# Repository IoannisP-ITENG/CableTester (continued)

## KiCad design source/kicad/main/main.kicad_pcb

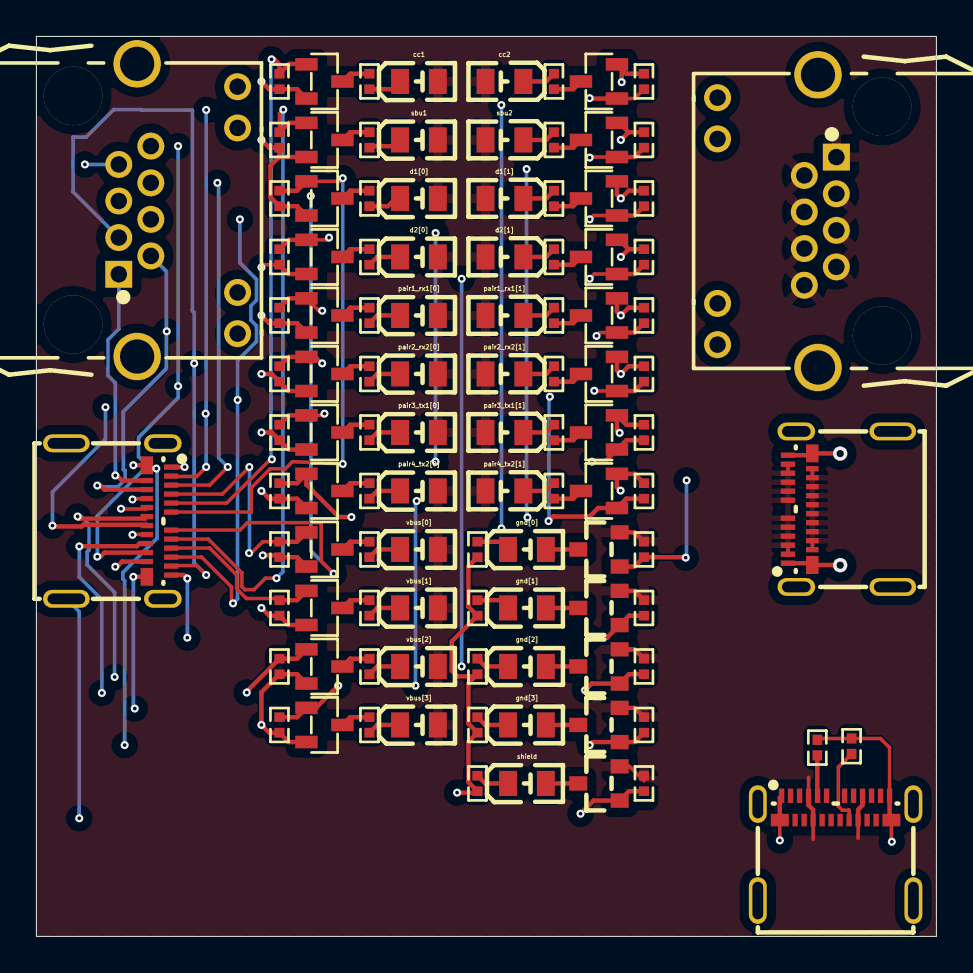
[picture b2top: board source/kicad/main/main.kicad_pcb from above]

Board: 4 copper layers, 50.0 x 50.0 mm, 107 parts (0 on the bottom side), 79 nets.

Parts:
psu.configuration_resistors[0][Resistor:5.0KΩ], psu.configuration_resistors[1][Resistor:5.0KΩ]: 5.0KΩ; R0402
psu.usb[USB_C_Receptacle:x]: x; USB-C-SMD_TYPE-C-USB-18
tester.cc1.indicator.led.current_limiting_resistor[Resistor:1KΩ], tester.cc2.indicator.led.current_limiting_resistor[Resistor:1KΩ], tester.d1[0].indicator.led.current_limiting_resistor[Resistor:1KΩ], tester.d1[1].indicator.led.current_limiting_resistor[Resistor:1KΩ], tester.d2[0].indicator.led.current_limiting_resistor[Resistor:1KΩ], tester.d2[1].indicator.led.current_limiting_resistor[Resistor:1KΩ], tester.gnd[0].indicator.led.current_limiting_resistor[Resistor:1KΩ], tester.gnd[1].indicator.led.current_limiting_resistor[Resistor:1KΩ], tester.gnd[2].indicator.led.current_limiting_resistor[Resistor:1KΩ], tester.gnd[3].indicator.led.current_limiting_resistor[Resistor:1KΩ], tester.pair1_rx1[0].indicator.led.current_limiting_resistor[Resistor:1KΩ], tester.pair1_rx1[1].indicator.led.current_limiting_resistor[Resistor:1KΩ], tester.pair2_rx2[0].indicator.led.current_limiting_resistor[Resistor:1KΩ], tester.pair2_rx2[1].indicator.led.current_limiting_resistor[Resistor:1KΩ], tester.pair3_tx1[0].indicator.led.current_limiting_resistor[Resistor:1KΩ], tester.pair3_tx1[1].indicator.led.current_limiting_resistor[Resistor:1KΩ], tester.pair4_tx2[0].indicator.led.current_limiting_resistor[Resistor:1KΩ], tester.pair4_tx2[1].indicator.led.current_limiting_resistor[Resistor:1KΩ], tester.sbu1.indicator.led.current_limiting_resistor[Resistor:1KΩ], tester.sbu2.indicator.led.current_limiting_resistor[Resistor:1KΩ], tester.shield.indicator.led.current_limiting_resistor[Resistor:1KΩ], tester.vbus[0].indicator.led.current_limiting_resistor[Resistor:1KΩ], tester.vbus[1].indicator.led.current_limiting_resistor[Resistor:1KΩ], tester.vbus[2].indicator.led.current_limiting_resistor[Resistor:1KΩ], tester.vbus[3].indicator.led.current_limiting_resistor[Resistor:1KΩ]: 1KΩ; R0402
tester.cc1.indicator.led.led[LED:D], tester.cc2.indicator.led.led[LED:D], tester.d1[0].indicator.led.led[LED:D], tester.d1[1].indicator.led.led[LED:D], tester.d2[0].indicator.led.led[LED:D], tester.d2[1].indicator.led.led[LED:D], tester.gnd[0].indicator.led.led[LED:D], tester.gnd[1].indicator.led.led[LED:D], tester.gnd[2].indicator.led.led[LED:D], tester.gnd[3].indicator.led.led[LED:D], tester.pair1_rx1[0].indicator.led.led[LED:D], tester.pair1_rx1[1].indicator.led.led[LED:D], tester.pair2_rx2[0].indicator.led.led[LED:D], tester.pair2_rx2[1].indicator.led.led[LED:D], tester.pair3_tx1[0].indicator.led.led[LED:D], tester.pair3_tx1[1].indicator.led.led[LED:D], tester.pair4_tx2[0].indicator.led.led[LED:D], tester.pair4_tx2[1].indicator.led.led[LED:D], tester.sbu1.indicator.led.led[LED:D], tester.sbu2.indicator.led.led[LED:D], tester.shield.indicator.led.led[LED:D], tester.vbus[0].indicator.led.led[LED:D], tester.vbus[1].indicator.led.led[LED:D], tester.vbus[2].indicator.led.led[LED:D], tester.vbus[3].indicator.led.led[LED:D]: D; LED0805-R-RD
tester.cc1.indicator.power_switch.mosfet[MOSFET:Q], tester.cc2.indicator.power_switch.mosfet[MOSFET:Q], tester.d1[0].indicator.power_switch.mosfet[MOSFET:Q], tester.d1[1].indicator.power_switch.mosfet[MOSFET:Q], tester.d2[0].indicator.power_switch.mosfet[MOSFET:Q], tester.d2[1].indicator.power_switch.mosfet[MOSFET:Q], tester.pair1_rx1[0].indicator.power_switch.mosfet[MOSFET:Q], tester.pair1_rx1[1].indicator.power_switch.mosfet[MOSFET:Q], tester.pair2_rx2[0].indicator.power_switch.mosfet[MOSFET:Q], tester.pair2_rx2[1].indicator.power_switch.mosfet[MOSFET:Q], tester.pair3_tx1[0].indicator.power_switch.mosfet[MOSFET:Q], tester.pair3_tx1[1].indicator.power_switch.mosfet[MOSFET:Q], tester.pair4_tx2[0].indicator.power_switch.mosfet[MOSFET:Q], tester.pair4_tx2[1].indicator.power_switch.mosfet[MOSFET:Q], tester.sbu1.indicator.power_switch.mosfet[MOSFET:Q], tester.sbu2.indicator.power_switch.mosfet[MOSFET:Q], tester.vbus[0].indicator.power_switch.mosfet[MOSFET:Q], tester.vbus[1].indicator.power_switch.mosfet[MOSFET:Q], tester.vbus[2].indicator.power_switch.mosfet[MOSFET:Q], tester.vbus[3].indicator.power_switch.mosfet[MOSFET:Q]: Q; SOT-23-3_L2.9-W1.3-P1.90-LS2.4-BR
tester.cc1.indicator.power_switch.pull_resistor[Resistor:100KΩ], tester.cc2.indicator.power_switch.pull_resistor[Resistor:100KΩ], tester.d1[0].indicator.power_switch.pull_resistor[Resistor:100KΩ], tester.d1[1].indicator.power_switch.pull_resistor[Resistor:100KΩ], tester.d2[0].indicator.power_switch.pull_resistor[Resistor:100KΩ], tester.d2[1].indicator.power_switch.pull_resistor[Resistor:100KΩ], tester.gnd[0].indicator.power_switch.pull_resistor[Resistor:100KΩ], tester.gnd[1].indicator.power_switch.pull_resistor[Resistor:100KΩ], tester.gnd[2].indicator.power_switch.pull_resistor[Resistor:100KΩ], tester.gnd[3].indicator.power_switch.pull_resistor[Resistor:100KΩ], tester.pair1_rx1[0].indicator.power_switch.pull_resistor[Resistor:100KΩ], tester.pair1_rx1[1].indicator.power_switch.pull_resistor[Resistor:100KΩ], tester.pair2_rx2[0].indicator.power_switch.pull_resistor[Resistor:100KΩ], tester.pair2_rx2[1].indicator.power_switch.pull_resistor[Resistor:100KΩ], tester.pair3_tx1[0].indicator.power_switch.pull_resistor[Resistor:100KΩ], tester.pair3_tx1[1].indicator.power_switch.pull_resistor[Resistor:100KΩ], tester.pair4_tx2[0].indicator.power_switch.pull_resistor[Resistor:100KΩ], tester.pair4_tx2[1].indicator.power_switch.pull_resistor[Resistor:100KΩ], tester.sbu1.indicator.power_switch.pull_resistor[Resistor:100KΩ], tester.sbu2.indicator.power_switch.pull_resistor[Resistor:100KΩ], tester.shield.indicator.power_switch.pull_resistor[Resistor:100KΩ], tester.vbus[0].indicator.power_switch.pull_resistor[Resistor:100KΩ], tester.vbus[1].indicator.power_switch.pull_resistor[Resistor:100KΩ], tester.vbus[2].indicator.power_switch.pull_resistor[Resistor:100KΩ], tester.vbus[3].indicator.power_switch.pull_resistor[Resistor:100KΩ]: 100KΩ; R0402
tester.gnd[0].indicator.power_switch.mosfet[MOSFET:Q], tester.gnd[1].indicator.power_switch.mosfet[MOSFET:Q], tester.gnd[2].indicator.power_switch.mosfet[MOSFET:Q], tester.gnd[3].indicator.power_switch.mosfet[MOSFET:Q], tester.shield.indicator.power_switch.mosfet[MOSFET:Q]: Q; SOT-23_L2.9-W1.3-P1.90-LS2.4-BR
tester.rj45[0][RJ45_Receptacle:x], tester.rj45[1][RJ45_Receptacle:x]: x; RJ45-TH_B-1-1
tester.usb_c[0][USB_C_Receptacle:x], tester.usb_c[1][USB_C_Receptacle:x]: x; USB-C-SMD_TYPE-C-USB-18

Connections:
psu.usb[USB_C_Receptacle:x]-psu.configuration_resistors[0][Resistor:5.0KΩ]: psu.configuration_resistors[0][Resistor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.1, psu.usb[USB_C_Receptacle:x].A5
psu.usb[USB_C_Receptacle:x]-psu.configuration_resistors[1][Resistor:5.0KΩ]: psu.configuration_resistors[1][Resistor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.1, psu.usb[USB_C_Receptacle:x].B5
tester.cc1.indicator.led.current_limiting_resistor[Resistor:1KΩ]-tester.cc1.ind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: tester.cc1.indicator.led.current_limiti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.2, tester.cc1.indicator.led.led[LED:D].2
tester.cc1.indicator.power_switch[PowerSwitch:virt]:5-tester.cc1.indicator.led[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: tester.cc1.indicator.led.current_limiti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.1, tester.cc1.indicator.power_switch.mosfe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.3
tester.cc1.indicator[LEDIndicator:virt]-tester.cc1.indicator.power_switch[Power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: tester.cc1.indicator.power_switch.mosfe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.1, tester.cc1.indicator.power_switch.pull_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.1, tester.usb_c[1][USB_C_Receptacle:x].A5
tester.cc2.indicator.led.led[LED:D]-tester.cc2.indicator.led.current_limiting_r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: tester.cc2.indicator.led.current_limiti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.2, tester.cc2.indicator.led.led[LED:D].2
tester.cc2.indicator.power_switch[PowerSwitch:virt]-tester.cc2.indicator[LEDInd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: tester.cc2.indicator.power_switch.mosfe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.1, tester.cc2.indicator.power_switch.pull_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.1, tester.usb_c[1][USB_C_Receptacle:x].B5
tester.cc2.indicator.power_switch[PowerSwitch:virt]:5-tester.cc2.indicator.led[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: tester.cc2.indicator.led.current_limiti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.1, tester.cc2.indicator.power_switch.mosfe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.3
tester.d1[0].indicator.led.current_limiting_resistor[Resistor:1KΩ]-tester.d1[0]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: tester.d1[0].indicator.led.current_limi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.2, tester.d1[0].indicator.led.led[LED:D].2
tester.d1[0].indicator.led[PoweredLED:virt]:2-tester.d1[0].indicator.power_swit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: tester.d1[0].indicator.led.current_limi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.1, tester.d1[0].indicator.power_switch.mos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.3
tester.d1[0].indicator[LEDIndicator:virt]-tester.d1[0].indicator.power_switch[P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: tester.d1[0].indicator.power_switch.mos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.1, tester.d1[0].indicator.power_switch.pul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.1, tester.usb_c[1][USB_C_Receptacle:x].A6
tester.d1[1].indicator.led.led[LED:D]-tester.d1[1].indicator.led.current_limiti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: tester.d1[1].indicator.led.current_limi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.2, tester.d1[1].indicator.led.led[LED:D].2
tester.d1[1].indicator.power_switch[PowerSwitch:virt]-tester.d1[1][PairTester:v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: tester.d1[1].indicator.power_switch.mos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.1, tester.d1[1].indicator.power_switch.pul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.1, tester.usb_c[1][USB_C_Receptacle:x].A7
tester.d1[1].indicator.power_switch[PowerSwitch:virt]:5-tester.d1[1].indicator.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: tester.d1[1].indicator.led.current_limi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.1, tester.d1[1].indicator.power_switch.mos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.3
tester.d2[0].indicator.led.current_limiting_resistor[Resistor:1KΩ]-tester.d2[0]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: tester.d2[0].indicator.led.current_limi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.2, tester.d2[0].indicator.led.led[LED:D].2
tester.d2[0].indicator.power_switch[PowerSwitch:virt]:5-tester.d2[0].indicator.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: tester.d2[0].indicator.led.current_limi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.1, tester.d2[0].indicator.power_switch.mos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.3
tester.d2[0][PairTester:virt]:4-tester.d2[0].indicator.power_switch[PowerSwitch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: tester.d2[0].indicator.power_switch.mos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.1, tester.d2[0].indicator.power_switch.pul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.1, tester.usb_c[1][USB_C_Receptacle:x].B6
tester.d2[1].indicator.led.current_limiting_resistor[Resistor:1KΩ]-tester.d2[1]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: tester.d2[1].indicator.led.current_limi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.2, tester.d2[1].indicator.led.led[LED:D].2
tester.d2[1].indicator.power_switch[PowerSwitch:virt]:5-tester.d2[1].indicator.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: tester.d2[1].indicator.led.current_limi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.1, tester.d2[1].indicator.power_switch.mos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.3
tester.d2[1][PairTester:virt]:4-tester.d2[1].indicator[LEDIndicator:virt]-teste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: tester.d2[1].indicator.power_switch.mos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.1, tester.d2[1].indicator.power_switch.pul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.1, tester.usb_c[1][USB_C_Receptacle:x].B7
tester.gnd[0].indicator.led.led[LED:D]-tester.gnd[0].indicator.led.current_limi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: tester.gnd[0].indicator.led.current_lim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.2, tester.gnd[0].indicator.led.led[LED:D].2
tester.gnd[0].indicator.power_switch[PowerSwitch:virt]-tester.gnd[0].indicator[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: tester.gnd[0].indicator.power_switch.mo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.1, tester.gnd[0].indicator.power_switch.pu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.1, tester.usb_c[1][USB_C_Receptacle:x].A1
tester.gnd[0].indicator.power_switch[PowerSwitch:virt]:4-tester.gnd[0].indicato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: tester.gnd[0].indicator.led.led[LED:D].1, tester.gnd[0].indicator.power_switch.mo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.3
tester.gnd[1].indicator.led.led[LED:D]-tester.gnd[1].indicator.led.current_limi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: tester.gnd[1].indicator.led.current_lim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.2, tester.gnd[1].indicator.led.led[LED:D].2
tester.gnd[1].indicator.power_switch[PowerSwitch:virt]:4-tester.gnd[1].indicato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: tester.gnd[1].indicator.led.led[LED:D].1, tester.gnd[1].indicator.power_switch.mo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.3
tester.gnd[1][PairTester:virt]:4-tester.gnd[1].indicator.power_switch[PowerSwit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: tester.gnd[1].indicator.power_switch.mo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.1, tester.gnd[1].indicator.power_switch.pu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.1, tester.usb_c[1][USB_C_Receptacle:x].A12
tester.gnd[2].indicator.led.led[LED:D]-tester.gnd[2].indicator.led.current_limi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: tester.gnd[2].indicator.led.current_lim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.2, tester.gnd[2].indicator.led.led[LED:D].2
tester.gnd[2].indicator.led[PoweredLED:virt]-tester.gnd[2].indicator.power_swit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: tester.gnd[2].indicator.led.led[LED:D].1, tester.gnd[2].indicator.power_switch.mo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.3
tester.gnd[2][PairTester:virt]:4-tester.gnd[2].indicator[LEDIndicator:virt]-tes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: tester.gnd[2].indicator.power_switch.mo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.1, tester.gnd[2].indicator.power_switch.pu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.1, tester.usb_c[1][USB_C_Receptacle:x].B1
tester.gnd[3].indicator.led.led[LED:D]-tester.gnd[3].indicator.led.current_limi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: tester.gnd[3].indicator.led.current_lim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.2, tester.gnd[3].indicator.led.led[LED:D].2
tester.gnd[3].indicator.led[PoweredLED:virt]-tester.gnd[3].indicator.power_swit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: tester.gnd[3].indicator.led.led[LED:D].1, tester.gnd[3].indicator.power_switch.mo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.3
tester.gnd[3][PairTester:virt]:4-tester.gnd[3].indicator[LEDIndicator:virt]-tes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: tester.gnd[3].indicator.power_switch.mo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.1, tester.gnd[3].indicator.power_switch.pu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.1, tester.usb_c[1][USB_C_Receptacle:x].B12
tester.pair1_rx1[0].indicator.led.led[LED:D]-tester.pair1_rx1[0].indicator.led.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: tester.pair1_rx1[0].indicator.led.curre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.2, tester.pair1_rx1[0].indicator.led.led[L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.2
tester.pair1_rx1[0].indicator.led[PoweredLED:virt]:2-tester.pair1_rx1[0].indica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: tester.pair1_rx1[0].indicator.led.curre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.1, tester.pair1_rx1[0].indicator.power_swi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.3
tester.pair1_rx1[0][PairTester:virt]:4-tester.pair1_rx1[0].indicator.power_swit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: tester.pair1_rx1[0].indicator.power_swi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.1, tester.pair1_rx1[0].indicator.power_swi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.1, tester.rj45[1][RJ45_Receptacle:x].1, tester.usb_c[1][USB_C_Receptacle:x].B11
tester.pair1_rx1[1].indicator.led.current_limiting_resistor[Resistor:1KΩ]-teste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: tester.pair1_rx1[1].indicator.led.curre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.2, tester.pair1_rx1[1].indicator.led.led[L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.2
tester.pair1_rx1[1].indicator.led[PoweredLED:virt]-tester.d2[1].indicator.power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: psu.usb[USB_C_Receptacle:x].A4, psu.usb[USB_C_Receptacle:x].A9, psu.usb[USB_C_Receptacle:x].B4, psu.usb[USB_C_Receptacle:x].B9, tester.cc1.indicator.led.led[LED:D].1, tester.cc2.indicator.led.led[LED:D].1, tester.d1[0].indicator.led.led[LED:D].1, tester.d1[1].indicator.led.led[LED:D].1, tester.d2[0].indicator.led.led[LED:D].1, tester.d2[1].indicator.led.led[LED:D].1, tester.gnd[0].indicator.power_switch.mo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.2, tester.gnd[0].indicator.power_switch.pu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.2, tester.gnd[1].indicator.power_switch.mo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.2, tester.gnd[1].indicator.power_switch.pu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.2, tester.gnd[2].indicator.power_switch.mo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.2, tester.gnd[2].indicator.power_switch.pu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.2, tester.gnd[3].indicator.power_switch.mo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.2, tester.gnd[3].indicator.power_switch.pu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.2, tester.pair1_rx1[0].indicator.led.led[L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.1, tester.pair1_rx1[1].indicator.led.led[L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.1, tester.pair2_rx2[0].indicator.led.led[L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.1, tester.pair2_rx2[1].indicator.led.led[L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.1, tester.pair3_tx1[0].indicator.led.led[L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.1, tester.pair3_tx1[1].indicator.led.led[L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.1, tester.pair4_tx2[0].indicator.led.led[L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.1, tester.pair4_tx2[1].indicator.led.led[L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.1, tester.rj45[0][RJ45_Receptacle:x].1, tester.rj45[0][RJ45_Receptacle:x].2, tester.rj45[0][RJ45_Receptacle:x].3, tester.rj45[0][RJ45_Receptacle:x].4, tester.rj45[0][RJ45_Receptacle:x].5, tester.rj45[0][RJ45_Receptacle:x].6, tester.rj45[0][RJ45_Receptacle:x].7, tester.rj45[0][RJ45_Receptacle:x].8, tester.sbu1.indicator.led.led[LED:D].1, tester.sbu2.indicator.led.led[LED:D].1, tester.shield.indicator.power_switch.mo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.2, tester.shield.indicator.power_switch.pu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.2, tester.usb_c[0][USB_C_Receptacle:x].A2, tester.usb_c[0][USB_C_Receptacle:x].A3, tester.usb_c[0][USB_C_Receptacle:x].A4, tester.usb_c[0][USB_C_Receptacle:x].A5, tester.usb_c[0][USB_C_Receptacle:x].A6, tester.usb_c[0][USB_C_Receptacle:x].A7, tester.usb_c[0][USB_C_Receptacle:x].A8, tester.usb_c[0][USB_C_Receptacle:x].A9, tester.usb_c[0][USB_C_Receptacle:x].A10, tester.usb_c[0][USB_C_Receptacle:x].A11, tester.usb_c[0][USB_C_Receptacle:x].B2, tester.usb_c[0][USB_C_Receptacle:x].B3, tester.usb_c[0][USB_C_Receptacle:x].B4, tester.usb_c[0][USB_C_Receptacle:x].B5, tester.usb_c[0][USB_C_Receptacle:x].B6, tester.usb_c[0][USB_C_Receptacle:x].B7, tester.usb_c[0][USB_C_Receptacle:x].B8, tester.usb_c[0][USB_C_Receptacle:x].B9, tester.usb_c[0][USB_C_Receptacle:x].B10, tester.usb_c[0][USB_C_Receptacle:x].B11, tester.vbus[0].indicator.led.led[LED:D].1, tester.vbus[1].indicator.led.led[LED:D].1, tester.vbus[2].indicator.led.led[LED:D].1, tester.vbus[3].indicator.led.led[LED:D].1
tester.pair1_rx1[1].indicator.power_switch[PowerSwitch:virt]:5-tester.pair1_rx1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: tester.pair1_rx1[1].indicator.led.curre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.1, tester.pair1_rx1[1].indicator.power_swi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.3
tester.pair1_rx1[1][PairTester:virt]:4-tester.pair1_rx1[1].indicator[LEDIndicat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: tester.pair1_rx1[1].indicator.power_swi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.1, tester.pair1_rx1[1].indicator.power_swi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.1, tester.rj45[1][RJ45_Receptacle:x].2, tester.usb_c[1][USB_C_Receptacle:x].B10
tester.pair2_rx2[0].indicator.led.led[LED:D]-tester.pair2_rx2[0].indicator.led.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: tester.pair2_rx2[0].indicator.led.curre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.2, tester.pair2_rx2[0].indicator.led.led[L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.2
tester.pair2_rx2[0].indicator.power_switch[PowerSwitch:virt]:5-tester.pair2_rx2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: tester.pair2_rx2[0].indicator.led.curre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.1, tester.pair2_rx2[0].indicator.power_swi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.3
tester.pair2_rx2[0].indicator[LEDIndicator:virt]-tester.pair2_rx2[0][PairTester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: tester.pair2_rx2[0].indicator.power_swi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.1, tester.pair2_rx2[0].indicator.power_swi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.1, tester.rj45[1][RJ45_Receptacle:x].3, tester.usb_c[1][USB_C_Receptacle:x].A11
tester.pair2_rx2[1].indicator.led.current_limiting_resistor[Resistor:1KΩ]-teste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: tester.pair2_rx2[1].indicator.led.curre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.2, tester.pair2_rx2[1].indicator.led.led[L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.2
tester.pair2_rx2[1].indicator.power_switch[PowerSwitch:virt]-tester.pair2_rx2[1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: tester.pair2_rx2[1].indicator.power_swi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.1, tester.pair2_rx2[1].indicator.power_swi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.1, tester.rj45[1][RJ45_Receptacle:x].4, tester.usb_c[1][USB_C_Receptacle:x].A10
tester.pair2_rx2[1].indicator.power_switch[PowerSwitch:virt]:5-tester.pair2_rx2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: tester.pair2_rx2[1].indicator.led.curre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.1, tester.pair2_rx2[1].indicator.power_swi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.3
tester.pair3_tx1[0].indicator.led.current_limiting_resistor[Resistor:1KΩ]-teste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: tester.pair3_tx1[0].indicator.led.curre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.2, tester.pair3_tx1[0].indicator.led.led[L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.2
tester.pair3_tx1[0].indicator.power_switch[PowerSwitch:virt]-tester.pair3_tx1[0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: tester.pair3_tx1[0].indicator.power_swi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.1, tester.pair3_tx1[0].indicator.power_swi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.1, tester.rj45[1][RJ45_Receptacle:x].5, tester.usb_c[1][USB_C_Receptacle:x].A2
tester.pair3_tx1[0].indicator.power_switch[PowerSwitch:virt]:5-tester.pair3_tx1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: tester.pair3_tx1[0].indicator.led.curre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.1, tester.pair3_tx1[0].indicator.power_swi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.3
tester.pair3_tx1[1].indicator.led.current_limiting_resistor[Resistor:1KΩ]-teste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: tester.pair3_tx1[1].indicator.led.curre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.2, tester.pair3_tx1[1].indicator.led.led[L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.2
tester.pair3_tx1[1].indicator.power_switch[PowerSwitch:virt]:5-tester.pair3_tx1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: tester.pair3_tx1[1].indicator.led.curre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.1, tester.pair3_tx1[1].indicator.power_swi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.3
tester.pair3_tx1[1].indicator[LEDIndicator:virt]-tester.pair3_tx1[1][PairTester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: tester.pair3_tx1[1].indicator.power_swi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.1, tester.pair3_tx1[1].indicator.power_swi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.1, tester.rj45[1][RJ45_Receptacle:x].6, tester.usb_c[1][USB_C_Receptacle:x].A3
tester.pair4_tx2[0].indicator.led.led[LED:D]-tester.pair4_tx2[0].indicator.led.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: tester.pair4_tx2[0].indicator.led.curre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.2, tester.pair4_tx2[0].indicator.led.led[L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.2
tester.pair4_tx2[0].indicator.power_switch[PowerSwitch:virt]:5-tester.pair4_tx2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: tester.pair4_tx2[0].indicator.led.curre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.1, tester.pair4_tx2[0].indicator.power_swi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.3
tester.pair4_tx2[0].indicator[LEDIndicator:virt]-tester.pair4_tx2[0].indicator.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: tester.pair4_tx2[0].indicator.power_swi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.1, tester.pair4_tx2[0].indicator.power_swi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.1, tester.rj45[1][RJ45_Receptacle:x].7, tester.usb_c[1][USB_C_Receptacle:x].B2
tester.pair4_tx2[1].indicator.led.led[LED:D]-tester.pair4_tx2[1].indicator.led.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: tester.pair4_tx2[1].indicator.led.curre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.2, tester.pair4_tx2[1].indicator.led.led[L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.2
tester.pair4_tx2[1].indicator.power_switch[PowerSwitch:virt]:5-tester.pair4_tx2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: tester.pair4_tx2[1].indicator.led.curre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.1, tester.pair4_tx2[1].indicator.power_swi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.3
tester.pair4_tx2[1].indicator[LEDIndicator:virt]-tester.pair4_tx2[1].indicator.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: tester.pair4_tx2[1].indicator.power_swi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.1, tester.pair4_tx2[1].indicator.power_swi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.1, tester.rj45[1][RJ45_Receptacle:x].8, tester.usb_c[1][USB_C_Receptacle:x].B3
tester.sbu1.indicator.led.led[LED:D]-tester.sbu1.indicator.led.current_limiting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: tester.sbu1.indicator.led.current_limit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.2, tester.sbu1.indicator.led.led[LED:D].2
tester.sbu1.indicator.led[PoweredLED:virt]:2-tester.sbu1.indicator.power_switch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: tester.sbu1.indicator.led.current_limit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.1, tester.sbu1.indicator.power_switch.mosf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.3
tester.sbu1.indicator[LEDIndicator:virt]-tester.sbu1.indicator.power_switch[Pow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: tester.sbu1.indicator.power_switch.mosf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.1, tester.sbu1.indicator.power_switch.pull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.1, tester.usb_c[1][USB_C_Receptacle:x].A8
tester.sbu2.indicator.led.led[LED:D]-tester.sbu2.indicator.led.current_limiting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: tester.sbu2.indicator.led.current_limit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.2, tester.sbu2.indicator.led.led[LED:D].2
tester.sbu2.indicator.power_switch[PowerSwitch:virt]-tester.sbu2[PairTester:vir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: tester.sbu2.indicator.power_switch.mosf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.1, tester.sbu2.indicator.power_switch.pull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.1, tester.usb_c[1][USB_C_Receptacle:x].B8
tester.sbu2.indicator.power_switch[PowerSwitch:virt]:5-tester.sbu2.indicator.le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: tester.sbu2.indicator.led.current_limit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.1, tester.sbu2.indicator.power_switch.mosf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.3
tester.shield.indicator.led.led[LED:D]-tester.shield.indicator.led.current_limi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: tester.shield.indicator.led.current_lim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.2, tester.shield.indicator.led.led[LED:D].2
tester.shield.indicator.led[PoweredLED:virt]-tester.shield.indicator.power_swit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: tester.shield.indicator.led.led[LED:D].1, tester.shield.indicator.power_switch.mo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.3
tester.shield.indicator.power_switch[PowerSwitch:virt]-tester.shield.indicator[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: tester.shield.indicator.power_switch.mo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.1, tester.shield.indicator.power_switch.pu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.1, tester.usb_c[1][USB_C_Receptacle:x].0
tester.vbus[0].indicator.led.led[LED:D]-tester.vbus[0].indicator.led.current_li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: tester.vbus[0].indicator.led.current_li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.2, tester.vbus[0].indicator.led.led[LED:D].2
tester.vbus[0].indicator.led[PoweredLED:virt]:2-tester.vbus[0].indicator.power_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: tester.vbus[0].indicator.led.current_li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.1, tester.vbus[0].indicator.power_switch.m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.3
tester.vbus[0][PairTester:virt]:4-tester.vbus[0].indicator[LEDIndicator:virt]-t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: tester.usb_c[1][USB_C_Receptacle:x].A4, tester.vbus[0].indicator.power_switch.m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.1, tester.vbus[0].indicator.power_switch.p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.1
tester.vbus[1].indicator.led.led[LED:D]-tester.vbus[1].indicator.led.current_li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: tester.vbus[1].indicator.led.current_li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.2, tester.vbus[1].indicator.led.led[LED:D].2
tester.vbus[1].indicator.power_switch[PowerSwitch:virt]:5-tester.vbus[1].indica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: tester.vbus[1].indicator.led.current_li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.1, tester.vbus[1].indicator.power_switch.m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.3
tester.vbus[1].indicator[LEDIndicator:virt]:3-tester.shield.indicator[LEDIndica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: psu.configuration_resistors[0][Resistor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.2, psu.configuration_resistors[1][Resistor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.2, psu.usb[USB_C_Receptacle:x].A1, psu.usb[USB_C_Receptacle:x].A12, psu.usb[USB_C_Receptacle:x].B1, psu.usb[USB_C_Receptacle:x].B12, tester.cc1.indicator.power_switch.mosfe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.2, tester.cc1.indicator.power_switch.pull_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.2, tester.cc2.indicator.power_switch.mosfe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.2, tester.cc2.indicator.power_switch.pull_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.2, tester.d1[0].indicator.power_switch.mos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.2, tester.d1[0].indicator.power_switch.pul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.2, tester.d1[1].indicator.power_switch.mos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.2, tester.d1[1].indicator.power_switch.pul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.2, tester.d2[0].indicator.power_switch.mos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.2, tester.d2[0].indicator.power_switch.pul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.2, tester.d2[1].indicator.power_switch.mos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.2, tester.d2[1].indicator.power_switch.pul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.2, tester.gnd[0].indicator.led.current_lim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.1, tester.gnd[1].indicator.led.current_lim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.1, tester.gnd[2].indicator.led.current_lim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.1, tester.gnd[3].indicator.led.current_lim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.1, tester.pair1_rx1[0].indicator.power_swi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.2, tester.pair1_rx1[0].indicator.power_swi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.2, tester.pair1_rx1[1].indicator.power_swi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.2, tester.pair1_rx1[1].indicator.power_swi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.2, tester.pair2_rx2[0].indicator.power_swi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.2, tester.pair2_rx2[0].indicator.power_swi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.2, tester.pair2_rx2[1].indicator.power_swi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.2, tester.pair2_rx2[1].indicator.power_swi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.2, tester.pair3_tx1[0].indicator.power_swi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.2, tester.pair3_tx1[0].indicator.power_swi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.2, tester.pair3_tx1[1].indicator.power_swi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.2, tester.pair3_tx1[1].indicator.power_swi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.2, tester.pair4_tx2[0].indicator.power_swi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.2, tester.pair4_tx2[0].indicator.power_swi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.2, tester.pair4_tx2[1].indicator.power_swi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.2, tester.pair4_tx2[1].indicator.power_swi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.2, tester.sbu1.indicator.power_switch.mosf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.2, tester.sbu1.indicator.power_switch.pull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.2, tester.sbu2.indicator.power_switch.mosf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.2, tester.sbu2.indicator.power_switch.pull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.2, tester.shield.indicator.led.current_lim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.1, tester.usb_c[0][USB_C_Receptacle:x].0, tester.usb_c[0][USB_C_Receptacle:x].A1, tester.usb_c[0][USB_C_Receptacle:x].A12, tester.usb_c[0][USB_C_Receptacle:x].B1, tester.usb_c[0][USB_C_Receptacle:x].B12, tester.vbus[0].indicator.power_switch.m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.2, tester.vbus[0].indicator.power_switch.p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.2, tester.vbus[1].indicator.power_switch.m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.2, tester.vbus[1].indicator.power_switch.p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.2, tester.vbus[2].indicator.power_switch.m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.2, tester.vbus[2].indicator.power_switch.p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.2, tester.vbus[3].indicator.power_switch.m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.2, tester.vbus[3].indicator.power_switch.p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.2
tester.vbus[1][PairTester:virt]:4-tester.vbus[1].indicator.power_switch[PowerSw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: tester.usb_c[1][USB_C_Receptacle:x].A9, tester.vbus[1].indicator.power_switch.m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.1, tester.vbus[1].indicator.power_switch.p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.1
tester.vbus[2].indicator.led.led[LED:D]-tester.vbus[2].indicator.led.current_li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: tester.vbus[2].indicator.led.current_li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.2, tester.vbus[2].indicator.led.led[LED:D].2
tester.vbus[2].indicator.led[PoweredLED:virt]:2-tester.vbus[2].indicator.power_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: tester.vbus[2].indicator.led.current_li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.1, tester.vbus[2].indicator.power_switch.m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.3
tester.vbus[2][PairTester:virt]:4-tester.vbus[2].indicator[LEDIndicator:virt]-t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: tester.usb_c[1][USB_C_Receptacle:x].B4, tester.vbus[2].indicator.power_switch.m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.1, tester.vbus[2].indicator.power_switch.p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.1
tester.vbus[3].indicator.led.current_limiting_resistor[Resistor:1KΩ]-tester.vbu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: tester.vbus[3].indicator.led.current_li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.2, tester.vbus[3].indicator.led.led[LED:D].2
tester.vbus[3].indicator.power_switch[PowerSwitch:virt]:5-tester.vbus[3].indica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: tester.vbus[3].indicator.led.current_li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.1, tester.vbus[3].indicator.power_switch.m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.3
tester.vbus[3][PairTester:virt]:4-tester.vbus[3].indicator.power_switch[PowerSw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: tester.usb_c[1][USB_C_Receptacle:x].B9, tester.vbus[3].indicator.power_switch.m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.1, tester.vbus[3].indicator.power_switch.p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.1

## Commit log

2023-01-05 Base schematic
2023-01-13 Add basic pcb placement; Add lcsc&pcb libs
2023-01-18 PCBTransformer & transformations
2023-01-18 Install pre-commit
2023-01-29 Routing
2023-05-02 Update requirements & Push dangling changes
2023-05-21 Add missing resistor values
2023-05-21 Finish routing & Fixing DRCs
2023-06-01 Bugfixes 1.0.0; WIP; Not exported yet.
    - Fixed USB-C PD resistors
    - Improved part-picking
    - Fixed LedIndicator (wrong PowerSwitch usage)
    - Reduced LED brightness
2023-06-01 Fix footprints/3dmodels
2023-06-01 Place labels
2023-06-01 bugfix/1.0.0 fixes (#3)
    * Bugfixes 1.0.0; WIP; Not exported yet.
    - Fixed USB-C PD resistors
    - Improved part-picking
    - Fixed LedIndicator (wrong PowerSwitch usage)
    - Reduced LED brightness
    * Fix footprints/3dmodels
2023-06-01 Documentation: Add render
2023-06-19 Bugfix: Add missing project documentation
2023-06-19 Add missing mini description
2023-06-19 Remove TODO notes
2023-06-26 Fix: Windows UTF-8 compatibility; factory return
2023-06-26 Doc: Add auto layout example
2023-06-26 Add screenshots
2023-06-26 Documentation: Bugfix: Add missing documentation (#4)
    * Bugfix: Add missing project documentation
    * Add missing mini description
    * Remove TODO notes
2023-06-26 Fix: Windows UTF-8 compatibility; factory return (#6)
2023-06-26 Documentation: Add power of faebryk example (#7)
    * Doc: Add auto layout example
    * Add screenshots
2023-07-04 WIP: Runs, but names are not the same
2023-10-02 Fix some leftover 2.0 migration problems
